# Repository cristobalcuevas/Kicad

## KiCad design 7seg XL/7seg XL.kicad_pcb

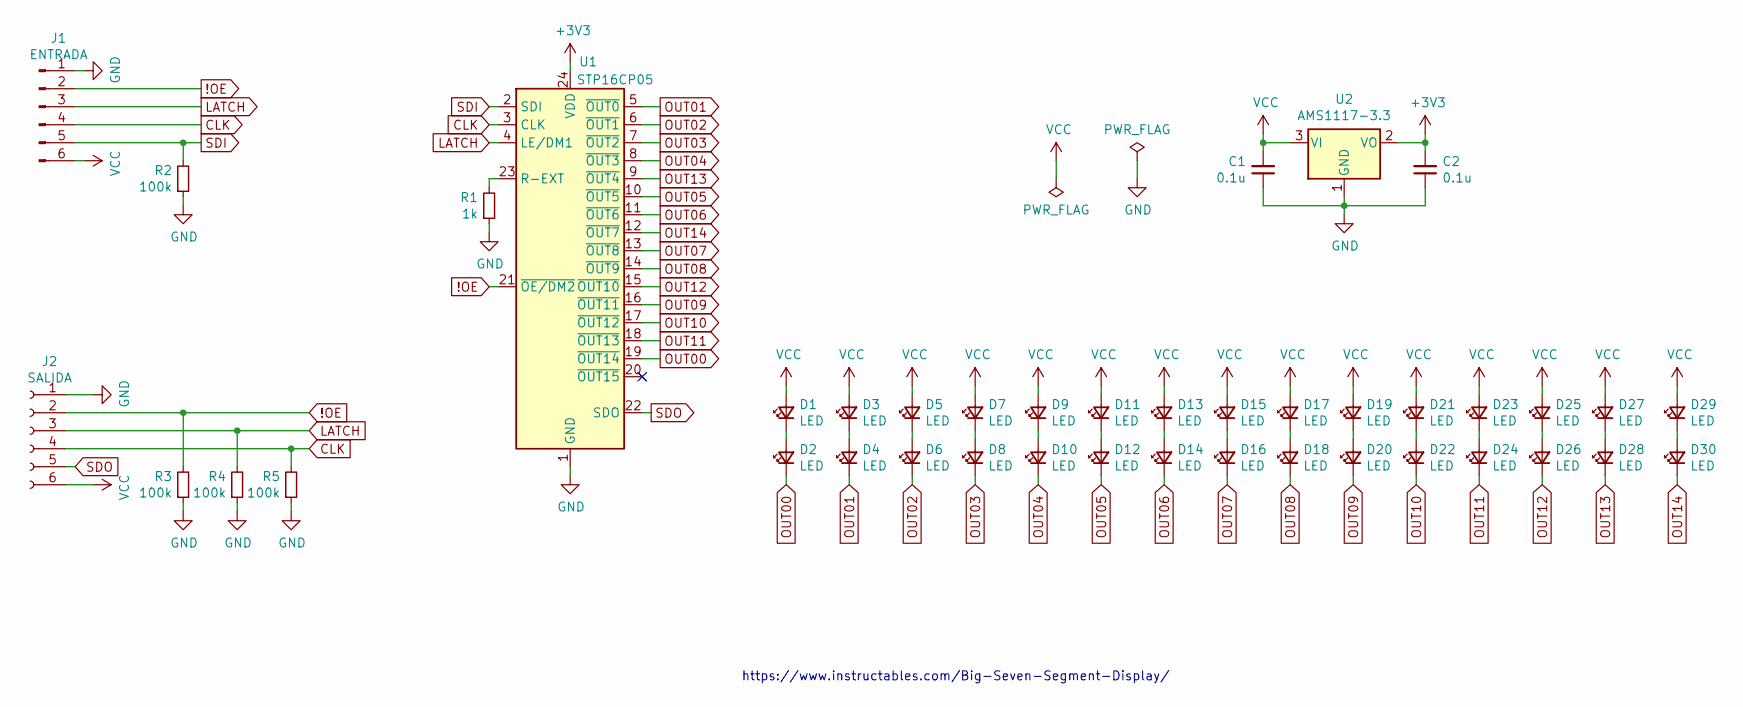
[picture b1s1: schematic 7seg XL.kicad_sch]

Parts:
C1, C2: 0.1u; C_1206_3216Metric
D1, D2, D3, D4, D5, D6, D7, D8, D9, D10, D11, D12, D13, D14, D15, D16, D17, D18, D19, D20, D21, D22, D23, D24, D25, D26, D27, D28, D29, D30: LED; LED_2010_5025Metric_Castellated
J1: ENTRADA; PinHeader_1x06_P2.54mm_Horizontal
J2: SALIDA; PinSocket_1x06_P2.54mm_Horizontal
R1: 1k; R_1206_3216Metric
R2, R3, R4, R5: 100k; R_1206_3216Metric
U1: STP16CP05; TSSOP-24_4.4x7.8mm_P0.65mm
U2: AMS1117-3.3; SOT-223-3_TabPin2

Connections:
!OE: J1.2, J2.2, R3.2, U1.21 (~OE/DM2)
+3V3: C2.2, U1.24 (VDD), U2.2 (VO)
CLK: J1.4, J2.4, R5.2, U1.3 (CLK)
GND: C1.1, C2.1, J1.1, J2.1, R1.1, R2.1, R3.1, R4.1, R5.1, U1.1 (GND), U2.1 (GND)
LATCH: J1.3, J2.3, R4.2, U1.4 (LE/DM1)
unnamed: D1.1 (K), D2.2 (A)
unnamed: D3.1 (K), D4.2 (A)
unnamed: D5.1 (K), D6.2 (A)
unnamed: D7.1 (K), D8.2 (A)
unnamed: D9.1 (K), D10.2 (A)
unnamed: D11.1 (K), D12.2 (A)
unnamed: D13.1 (K), D14.2 (A)
unnamed: D15.1 (K), D16.2 (A)
unnamed: D17.1 (K), D18.2 (A)
unnamed: D19.1 (K), D20.2 (A)
unnamed: D21.1 (K), D22.2 (A)
unnamed: D23.1 (K), D24.2 (A)
unnamed: D25.1 (K), D26.2 (A)
unnamed: D27.1 (K), D28.2 (A)
unnamed: D29.1 (K), D30.2 (A)
unnamed: R1.2, U1.23 (R-EXT)
OUT00: D2.1 (K), U1.19 (~OUT14)
OUT01: D4.1 (K), U1.5 (~OUT0)
OUT02: D6.1 (K), U1.6 (~OUT1)
OUT03: D8.1 (K), U1.7 (~OUT2)
OUT04: D10.1 (K), U1.8 (~OUT3)
OUT05: D12.1 (K), U1.10 (~OUT5)
OUT06: D14.1 (K), U1.11 (~OUT6)
OUT07: D16.1 (K), U1.13 (~OUT8)
OUT08: D18.1 (K), U1.14 (~OUT9)
OUT09: D20.1 (K), U1.16 (~OUT11)
OUT10: D22.1 (K), U1.17 (~OUT12)
OUT11: D24.1 (K), U1.18 (~OUT13)
OUT12: D26.1 (K), U1.15 (~OUT10)
OUT13: D28.1 (K), U1.9 (~OUT4)
OUT14: D30.1 (K), U1.12 (~OUT7)
SDI: J1.5, R2.2, U1.2 (SDI)
SDO: J2.5, U1.22 (SDO)
VCC: C1.2, D1.2 (A), D3.2 (A), D5.2 (A), D7.2 (A), D9.2 (A), D11.2 (A), D13.2 (A), D15.2 (A), D17.2 (A), D19.2 (A), D21.2 (A), D23.2 (A), D25.2 (A), D27.2 (A), D29.2 (A), J1.6, J2.6, U2.3 (VI)

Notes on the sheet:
https://www.instructables.com/Big-Seven-Segment-Display/

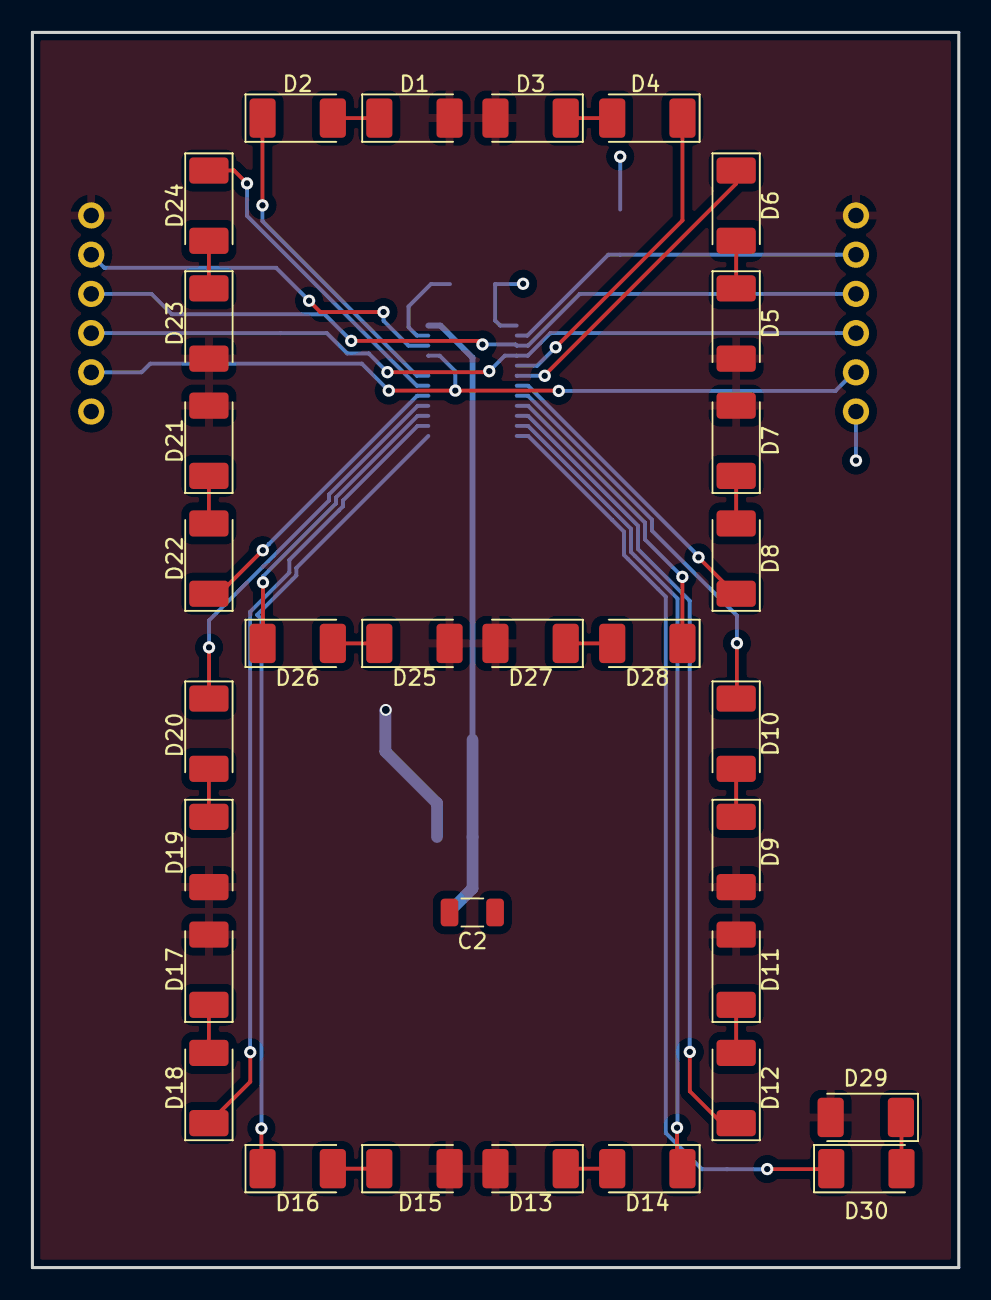
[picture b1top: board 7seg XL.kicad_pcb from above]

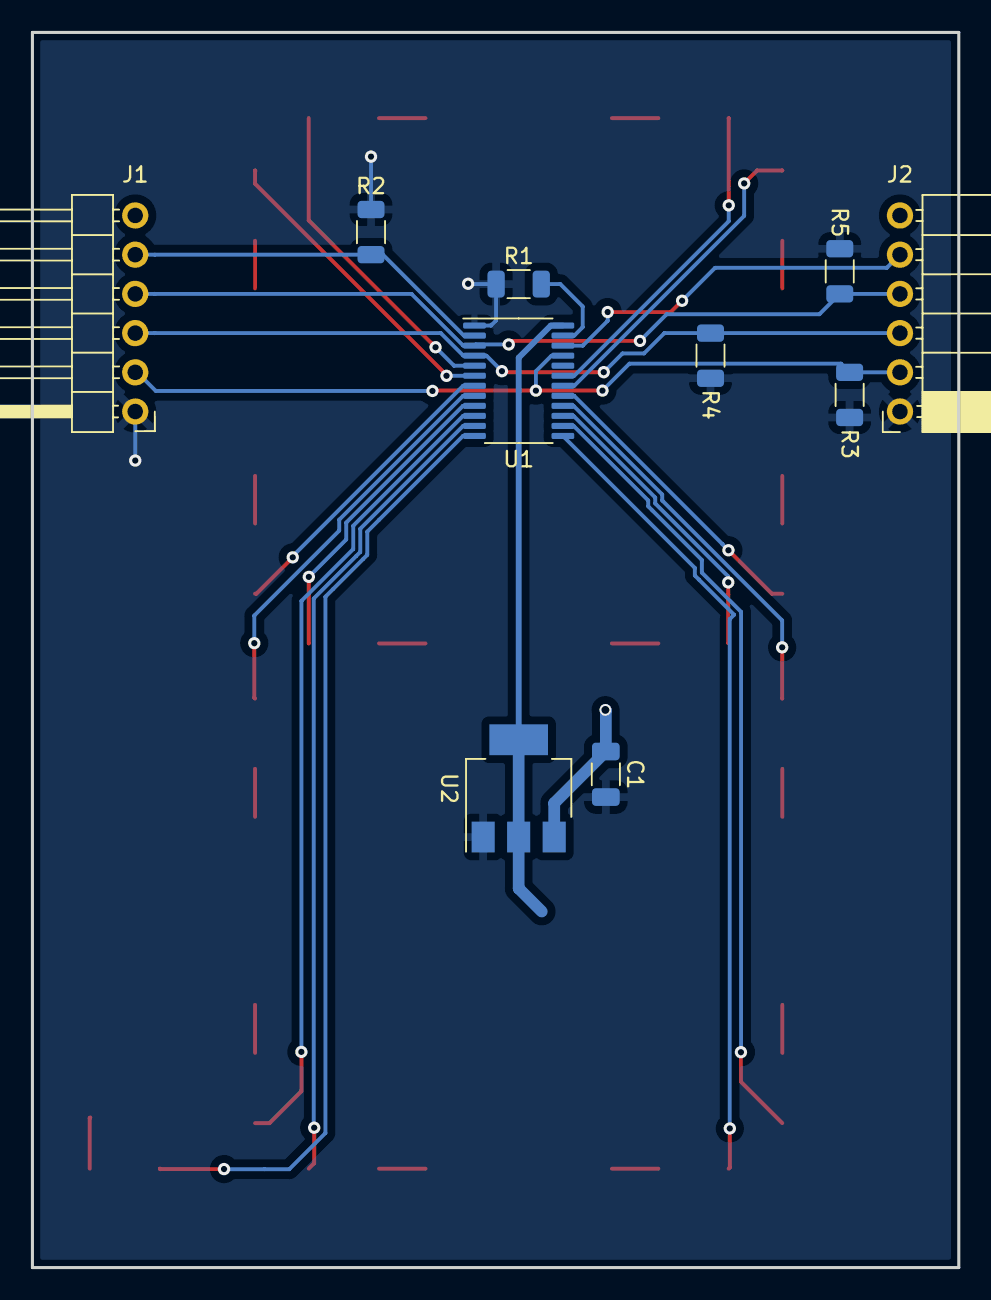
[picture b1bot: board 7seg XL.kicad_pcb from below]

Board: 2 copper layers, 60.0 x 80.0 mm, 41 parts (10 on the bottom side), 39 nets.

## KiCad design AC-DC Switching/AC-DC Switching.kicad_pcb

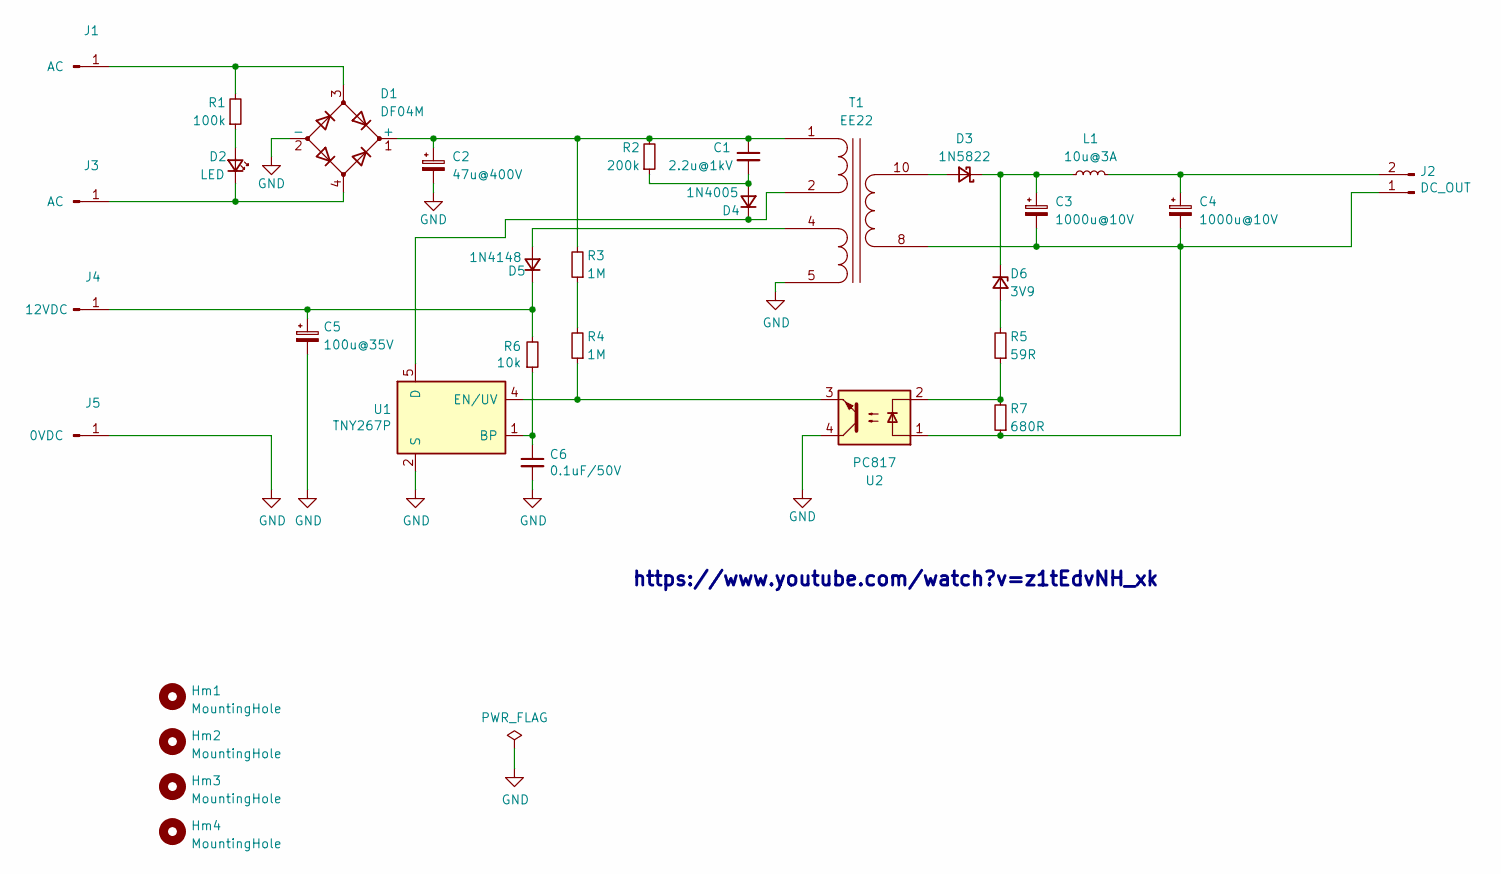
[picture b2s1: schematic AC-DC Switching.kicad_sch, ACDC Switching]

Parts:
C1: 2.2u@1kV; C_Disc_D10.5mm_W5.0mm_P5.00mm
C2: 47u@400V; CP_Radial_D10.0mm_P5.00mm
C3, C4: 1000u@10V; CP_Radial_D12.5mm_P5.00mm
C5: 100u@35V; CP_Radial_D10.0mm_P5.00mm
C6: 0.1uF/50V; C_Rect_L7.2mm_W3.5mm_P5.00mm_FKS2_FKP2_MKS2_MKP2
D1: DF04M; Diode_Bridge_DIP-4_W7.62mm_P5.08mm
D2: LED; LED_D3.0mm
D3: 1N5822; D_DO-201AD_P15.24mm_Horizontal
D4: 1N4005; D_DO-15_P12.70mm_Horizontal
D5: 1N4148; D_DO-34_SOD68_P7.62mm_Horizontal
D6: 3V9; D_DO-41_SOD81_P10.16mm_Horizontal
Hm1, Hm2, Hm3, Hm4: MountingHole; MountingHole_3.2mm_M3
J1, J3: AC
J2: DC_OUT; Molex_KK-254_AE-6410-02A_1x02_P2.54mm_Vertical
J4: 12VDC; TestPoint_Pad_D1.0mm
J5: 0VDC; TestPoint_Pad_D1.0mm
L1: 10u@3A; L_Toroid_Vertical_L21.6mm_W9.1mm_P8.40mm_Bourns_5700
R1: 100k; R_Axial_DIN0207_L6.3mm_D2.5mm_P10.16mm_Horizontal
R2: 200k; R_Axial_DIN0207_L6.3mm_D2.5mm_P10.16mm_Horizontal
R3, R4: 1M; R_Axial_DIN0207_L6.3mm_D2.5mm_P10.16mm_Horizontal
R5: 59R; R_Axial_DIN0207_L6.3mm_D2.5mm_P10.16mm_Horizontal
R6: 10k; R_Axial_DIN0207_L6.3mm_D2.5mm_P10.16mm_Horizontal
R7: 680R; R_Axial_DIN0207_L6.3mm_D2.5mm_P10.16mm_Horizontal
T1: EE22; Transformer_Myrra_EF20_7408x
U1: TNY267P; PowerIntegrations_PDIP-8B
U2: PC817; DIP-4_W7.62mm

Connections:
GND: C2.2, C5.2, C6.2, D1.2 (-), J5.1, T1.5 (SA), U1.2 (S), U1.3 (S), U1.7 (S), U1.8 (S), U2.4
unnamed: C1.1, C2.1, D1.1 (+), R2.2, R3.2, T1.1 (SD)
unnamed: C1.2, D4.2 (A), R2.1
unnamed: C3.1, D3.1 (K), D6.1 (K), L1.1
unnamed: C3.2, C4.2, J2.1, R7.1, T1.8 (AA), U2.1
unnamed: C4.1, J2.2, L1.2
unnamed: C5.1, D5.1 (K), J4.1, R6.2
unnamed: C6.1, R6.1, U1.1 (BP)
unnamed: D1.3, J1.1, R1.2
unnamed: D1.4, D2.1 (K), J3.1
unnamed: D2.2 (A), R1.1
unnamed: D3.2 (A), T1.10 (AB)
unnamed: D4.1 (K), T1.2 (SC), U1.5 (D)
unnamed: D5.2 (A), T1.4 (SB)
unnamed: D6.2 (A), R5.2
unnamed: R3.1, R4.2
unnamed: R4.1, U1.4 (EN/UV), U2.3
unnamed: R5.1, R7.2, U2.2

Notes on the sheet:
https://www.youtube.com/watch?v=z1tEdvNH_xk

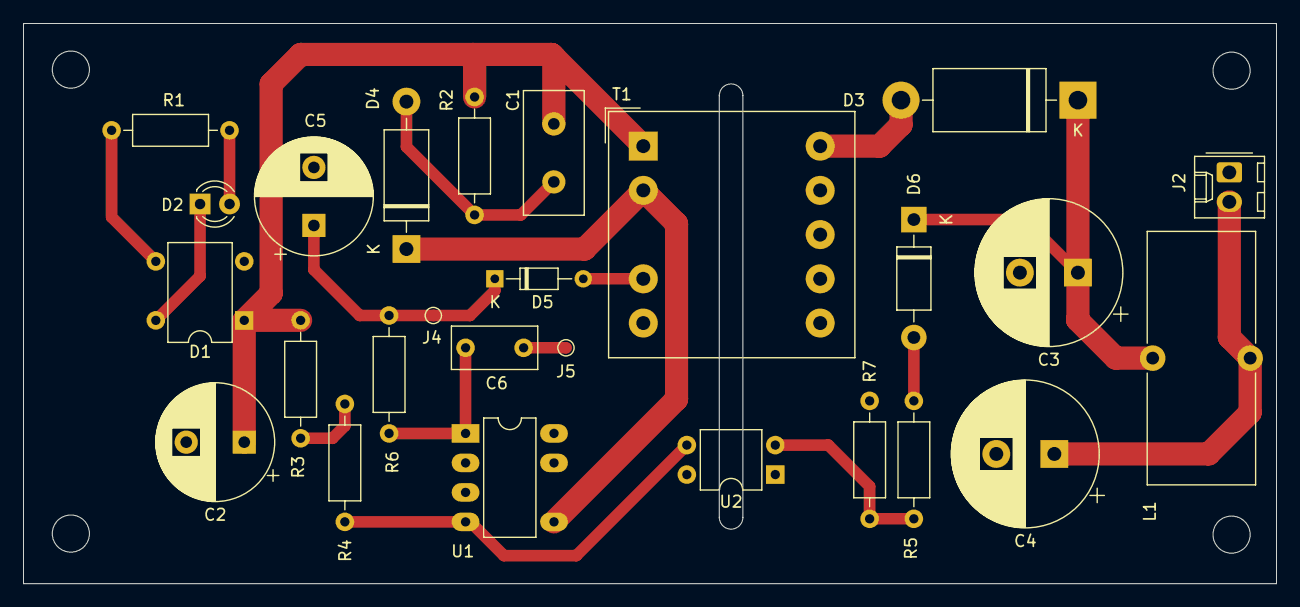
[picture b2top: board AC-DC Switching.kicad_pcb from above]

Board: 2 copper layers, 108.0 x 48.3 mm, 30 parts (0 on the bottom side), 18 nets.

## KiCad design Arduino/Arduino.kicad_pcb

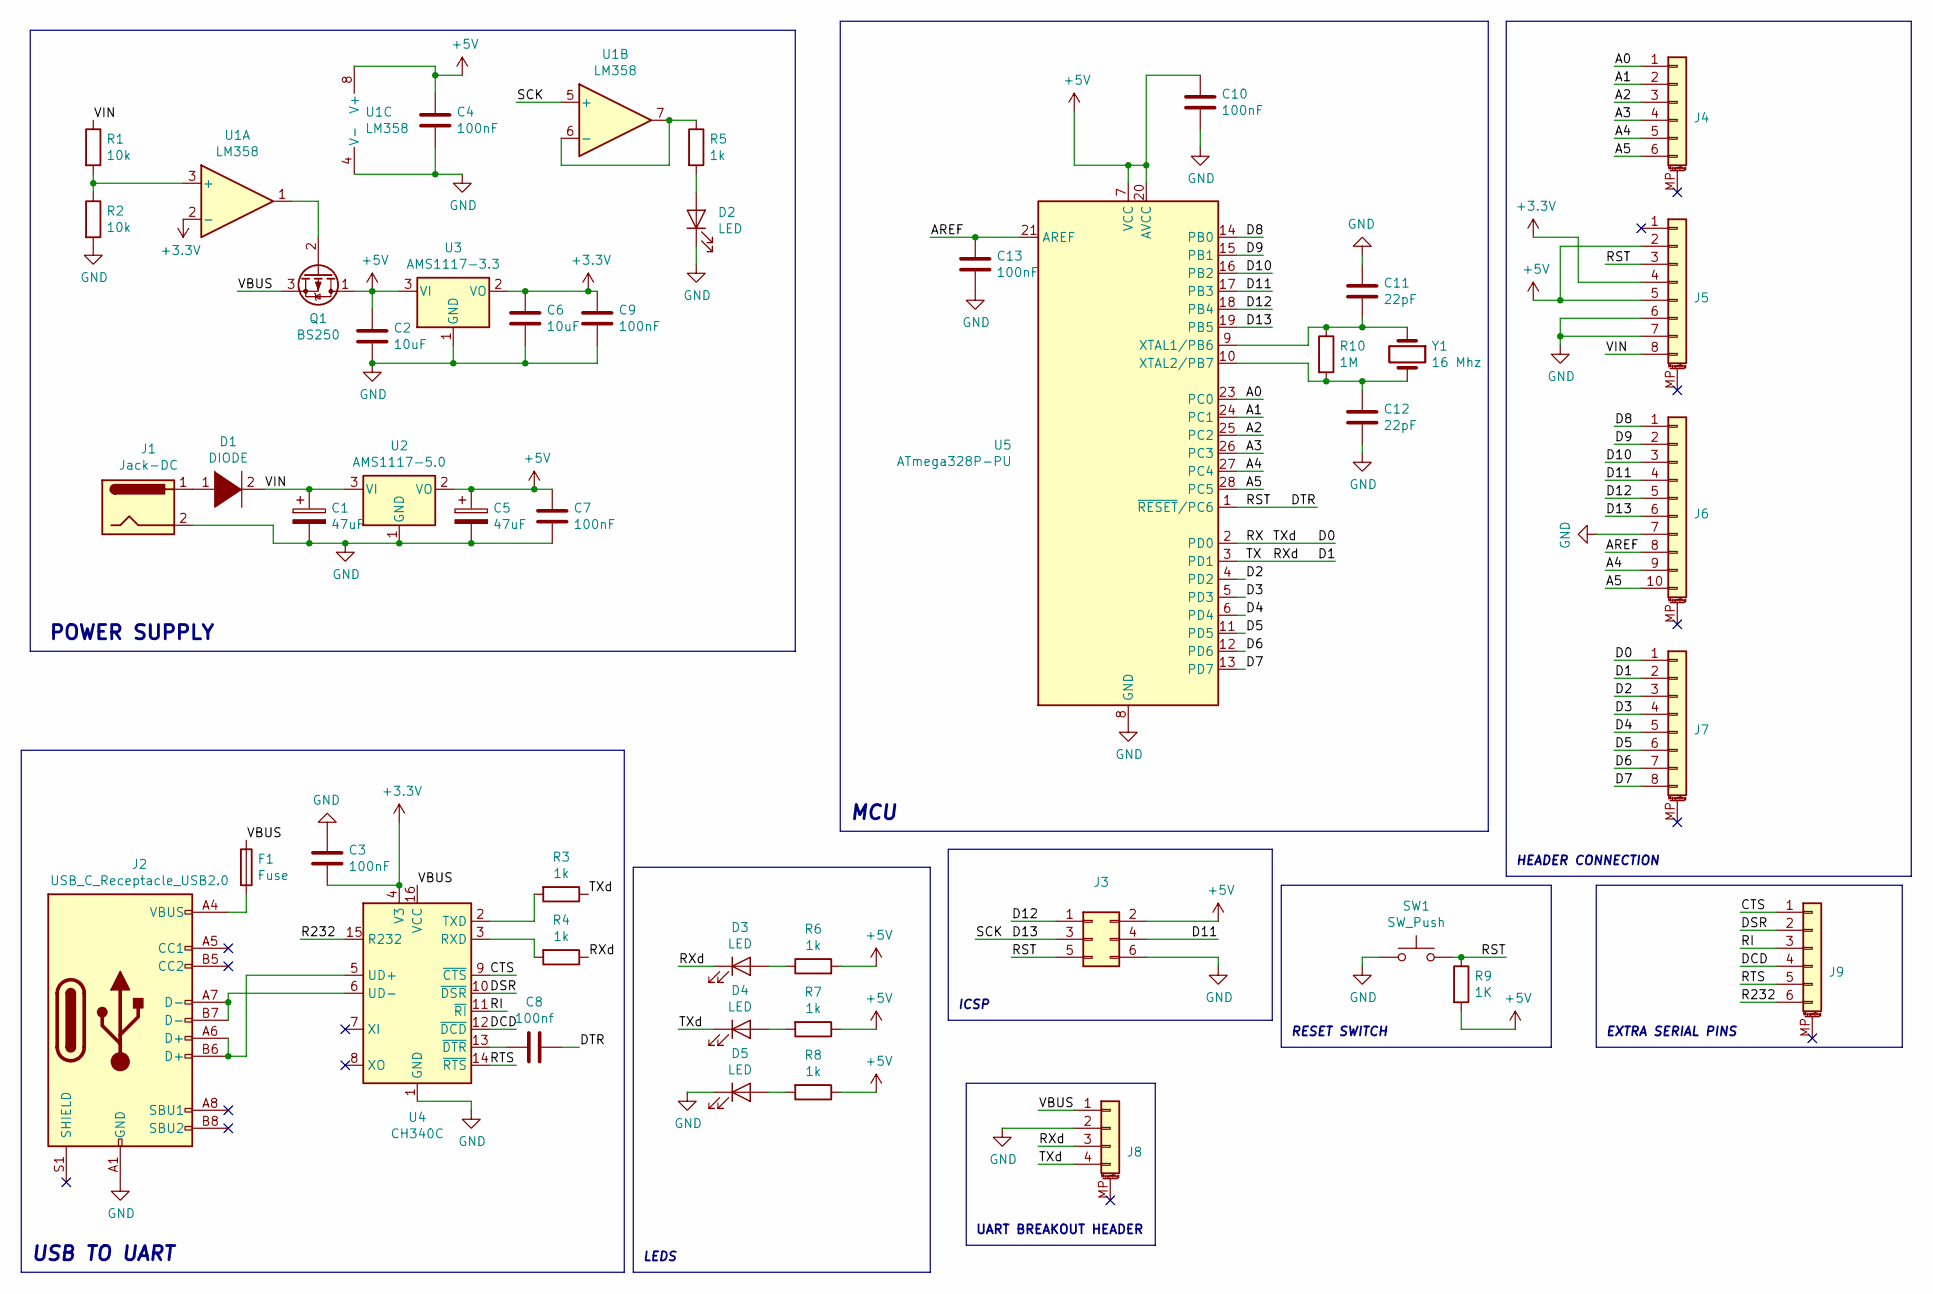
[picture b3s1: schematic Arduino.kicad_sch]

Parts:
C1, C5: 47uF
C2, C6: 10uF
C3, C4, C7, C9, C10, C13: 100nF
C8: 100nf
C11, C12: 22pF
D1: DIODE
D2, D3, D4, D5: LED
F1: Fuse
J1: Jack-DC
J2: USB_C_Receptacle_USB2.0
J3: Conn_02x03_Odd_Even
J4, J9: Conn_01x06_MountingPin
J5, J7: Conn_01x08_MountingPin
J6: Conn_01x10_MountingPin
J8: Conn_01x04_MountingPin
Q1: BS250; TO-92_Inline
R1, R2: 10k
R3, R4, R5, R6, R7, R8: 1k
R9: 1K
R10: 1M
SW1: SW_Push
U1: LM358
U2: AMS1117-5.0; SOT-223-3_TabPin2
U3: AMS1117-3.3; SOT-223-3_TabPin2
U4: CH340C; SOIC-16_3.9x9.9mm_P1.27mm
U5: ATmega328P-PU; DIP-28_W7.62mm
Y1: 16 Mhz

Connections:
+3V3: C3.2, C6.1, C9.1, J5.4, U1.2 (-), U3.2 (VO), U4.4 (V3)
/A0: J4.1, U5.23 (PC0)
/A1: J4.2, U5.24 (PC1)
/A2: J4.3, U5.25 (PC2)
/A3: J4.4, U5.26 (PC3)
/A4: J4.5, J6.9, U5.27 (PC4)
/A5: J4.6, J6.10, U5.28 (PC5)
/AREF: C13.1, J6.8, U5.21 (AREF)
/CTS: J9.1, U4.9 (~CTS)
/D0: D4.1 (K), J7.1, J8.4, R3.1, U5.2 (PD0)
/D1: D3.1 (K), J7.2, J8.3, R4.1, U5.3 (PD1)
/D2: J7.3, U5.4 (PD2)
/D3: J7.4, U5.5 (PD3)
/D4: J7.5, U5.6 (PD4)
/D5: J7.6, U5.11 (PD5)
/D6: J7.7, U5.12 (PD6)
/D7: J7.8, U5.13 (PD7)
/D8: J6.1, U5.14 (PB0)
/D9: J6.2, U5.15 (PB1)
/D10: J6.3, U5.16 (PB2)
/D11: J3.4, J6.4, U5.17 (PB3)
/D12: J3.1, J6.5, U5.18 (PB4)
/D13: J3.3, J6.6, U1.5 (+), U5.19 (PB5)
/DCD: J9.4, U4.12 (~DCD)
/DSR: J9.2, U4.10 (~DSR)
/DTR: C8.1, J3.5, J5.3, R9.1, SW1.2, U5.1 (~RESET/PC6)
/R232: J9.6, U4.15 (R232)
/RI: J9.3, U4.11 (~RI)
/RTS: J9.5, U4.14 (~RTS)
/VBUS: F1.1, J8.1, Q1.3 (S), U4.16 (VCC)
/VIN: C1.1, D1.2 (A), J5.8, R1.1, U2.3 (VI)
GND: C1.2, C2.2, C3.1, C4.2, C5.2, C6.2, C7.2, C9.2, C10.2, C11.1, C12.2, C13.2, D2.1 (K), D5.1 (K), J1.2, J2.A1 (GND), J2.A12 (GND), J2.B1 (GND), J2.B12 (GND), J3.6, J5.6, J5.7, J6.7, J8.2, R2.2, SW1.1, U1.4 (V-), U2.1 (GND), U3.1 (GND), U4.1 (GND), U5.8 (GND), U5.22 (GND); also elsewhere on the board
unnamed: C8.2, U4.13 (~DTR)
unnamed: C11.2, R10.1, U5.9 (XTAL1/PB6), Y1.1
unnamed: C12.1, R10.2, U5.10 (XTAL2/PB7), Y1.2
unnamed: D1.1 (K), J1.1
unnamed: D2.2 (A), R5.2
unnamed: D3.2 (A), R6.1
unnamed: D4.2 (A), R7.2
unnamed: D5.2 (A), R8.2
unnamed: F1.2, J2.A4 (VBUS), J2.A9 (VBUS), J2.B4 (VBUS), J2.B9 (VBUS)
unnamed: J2.A6 (D+), J2.B6 (D+), U4.5 (UD+)
unnamed: J2.A7 (D-), J2.B7 (D-), U4.6 (UD-)
unnamed: R1.2, R2.1, U1.3 (+)
unnamed: R3.2, U4.2 (TXD)
unnamed: R4.2, U4.3 (RXD)
unnamed: R5.1, U1.6 (-), U1.7

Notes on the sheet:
HEADER CONNECTION
LEDS
ICSP
RESET SWITCH
MCU
UART BREAKOUT HEADER
USB TO UART
EXTRA SERIAL PINS
POWER SUPPLY

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
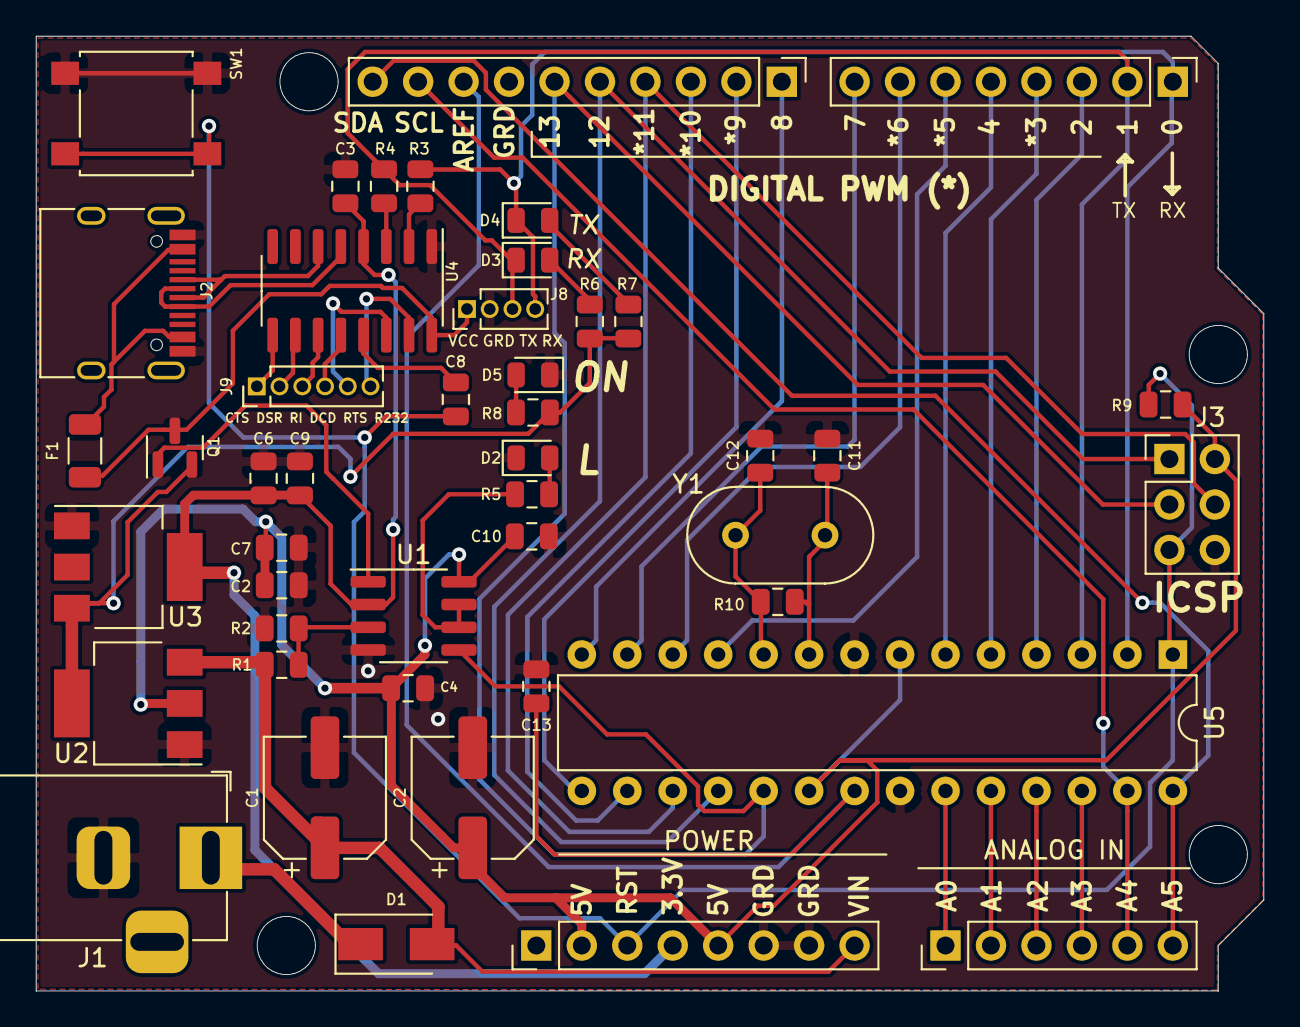
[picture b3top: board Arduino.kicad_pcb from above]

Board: 2 copper layers, 68.6 x 53.3 mm, 46 parts (0 on the bottom side), 49 nets.

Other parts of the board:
C2#2: 10uF; CP_Elec_6.3x5.4

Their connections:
GND: C2#2.2; also elsewhere on the board

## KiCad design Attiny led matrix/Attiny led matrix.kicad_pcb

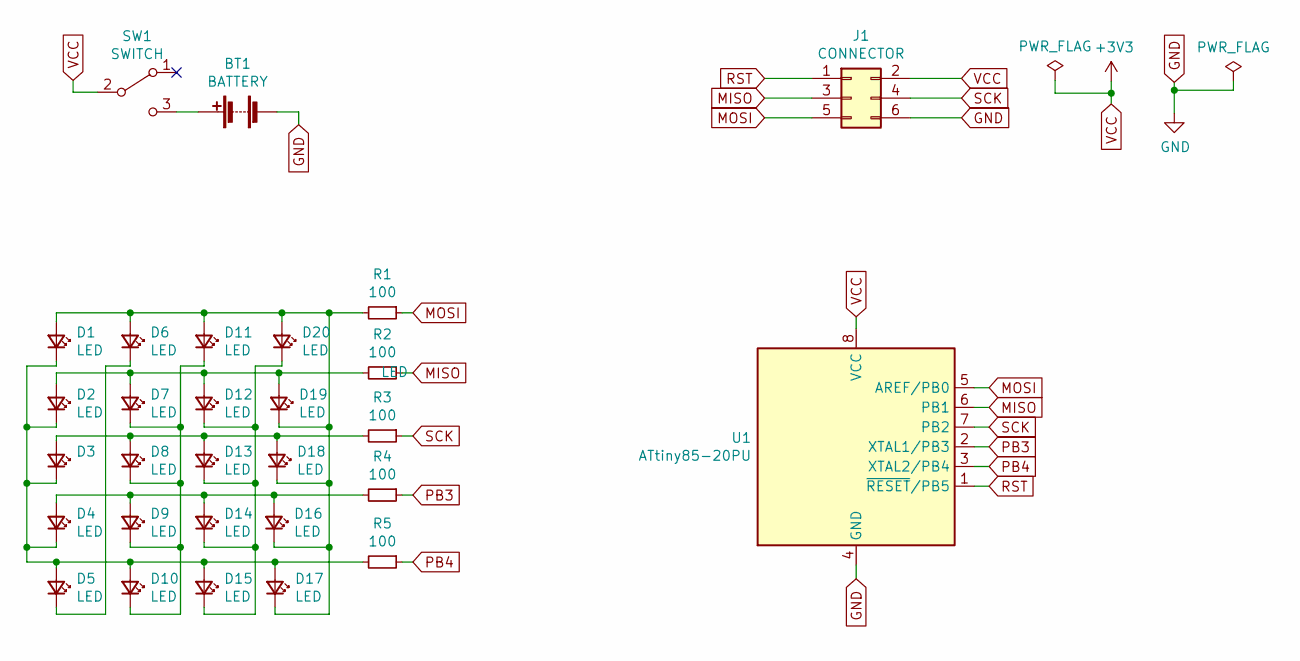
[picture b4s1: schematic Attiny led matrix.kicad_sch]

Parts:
BT1: BATTERY; BatteryHolder_Keystone_103_1x20mm
D1, D2, D3, D4, D5, D6, D7, D8, D9, D10, D11, D12, D13, D14, D15, D16, D17, D18, D19, D20: LED; LED_D3.0mm
J1: CONNECTOR; PinHeader_2x03_P2.54mm_Vertical
R1, R2, R3, R4, R5: 100; R_Axial_DIN0204_L3.6mm_D1.6mm_P5.08mm_Horizontal
SW1: SWITCH; SW_CuK_JS202011CQN_DPDT_Straight
U1: ATtiny85-20PU; DIP-8_W7.62mm

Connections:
GND: BT1.2 (-), J1.6, U1.4 (GND)
MISO: J1.3, R2.1, U1.6 (PB1)
MOSI: J1.5, R1.1, U1.5 (AREF/PB0)
unnamed: BT1.1 (+), SW1.3 (C)
unnamed: D1.1 (K), D2.1 (K), D3.1 (K), D4.1 (K), D5.2 (A), D10.2 (A), D15.2 (A), D17.2 (A), R5.2
unnamed: D1.2 (A), D6.2 (A), D11.2 (A), D16.1 (K), D17.1 (K), D18.1 (K), D19.1 (K), D20.2 (A), R1.2
unnamed: D5.1 (K), D6.1 (K)
unnamed: D7.1 (K), D8.1 (K), D9.1 (K), D10.1 (K), D11.1 (K)
unnamed: D12.1 (K), D13.1 (K), D14.1 (K), D15.1 (K), D20.1 (K)
unnamed: D2.2 (A), D7.2 (A), D12.2 (A), D19.2 (A), R2.2
unnamed: D3.2 (A), D8.2 (A), D13.2 (A), D18.2 (A), R3.2
unnamed: D4.2 (A), D9.2 (A), D14.2 (A), D16.2 (A), R4.2
PB3: R4.1, U1.2 (XTAL1/PB3)
PB4: R5.1, U1.3 (XTAL2/PB4)
RST: J1.1, U1.1 (~RESET/PB5)
SCK: J1.4, R3.1, U1.7 (PB2)
VCC: J1.2, SW1.2 (B), U1.8 (VCC)

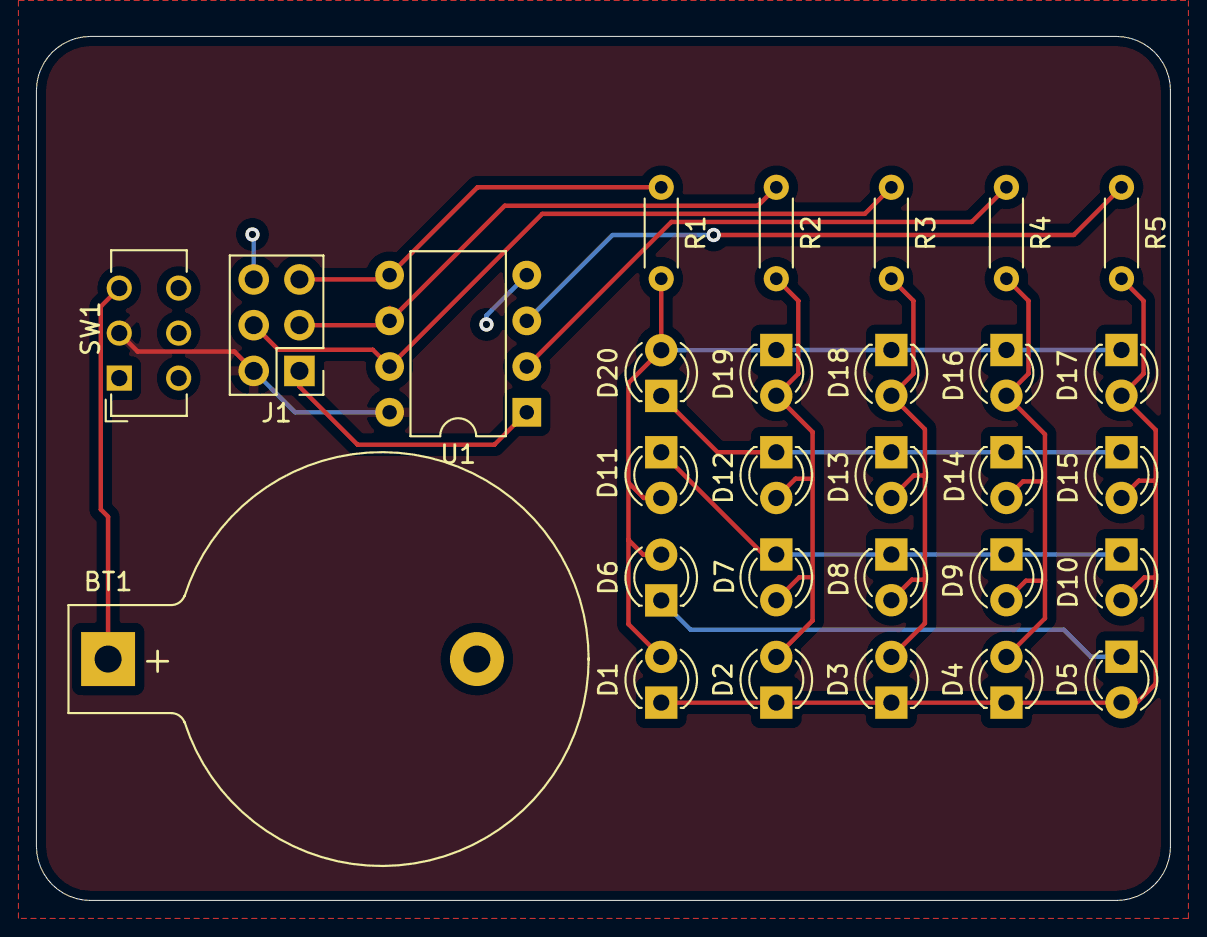
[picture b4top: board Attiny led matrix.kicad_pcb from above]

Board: 2 copper layers, 63.0 x 48.0 mm, 29 parts (0 on the bottom side), 17 nets.

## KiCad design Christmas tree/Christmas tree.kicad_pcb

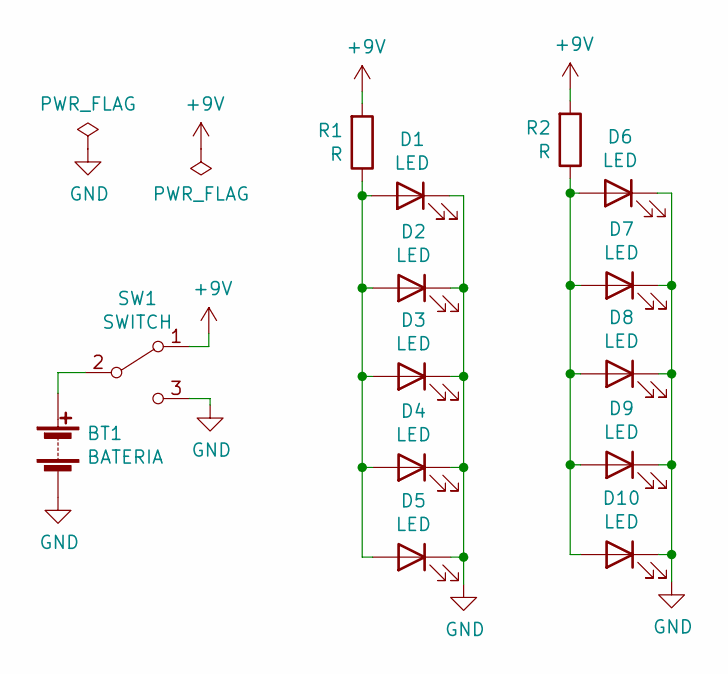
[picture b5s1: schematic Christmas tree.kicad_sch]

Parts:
BT1: BATERIA; PinHeader_1x02_P2.54mm_Vertical
D1, D2, D3, D4, D5, D6, D7, D8, D9, D10: LED; LED_D5.0mm
R1, R2: R; R_Axial_DIN0204_L3.6mm_D1.6mm_P5.08mm_Horizontal
SW1: SWITCH; SW_E-Switch_EG1224_SPDT_Angled

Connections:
+9V: R1.2, R2.2, SW1.1 (A)
GND: BT1.2 (-), D1.1 (K), D2.1 (K), D3.1 (K), D4.1 (K), D5.1 (K), D6.1 (K), D7.1 (K), D8.1 (K), D9.1 (K), D10.1 (K), SW1.3 (C)
unnamed: BT1.1 (+), SW1.2 (B)
unnamed: D1.2 (A), D2.2 (A), D3.2 (A), D4.2 (A), D5.2 (A), R1.1
unnamed: D6.2 (A), D7.2 (A), D8.2 (A), D9.2 (A), D10.2 (A), R2.1

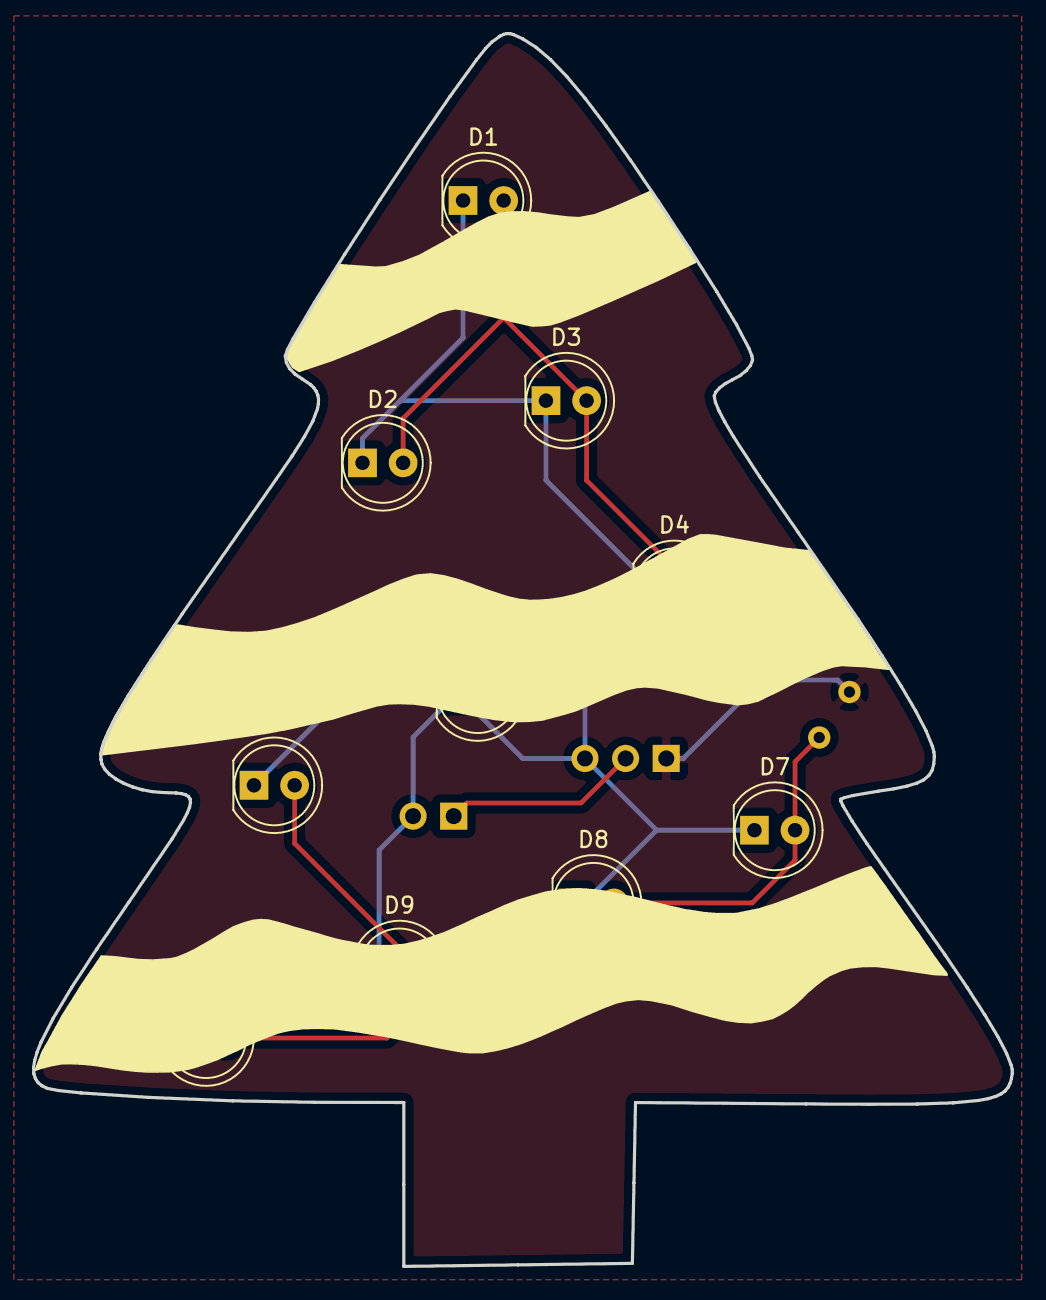
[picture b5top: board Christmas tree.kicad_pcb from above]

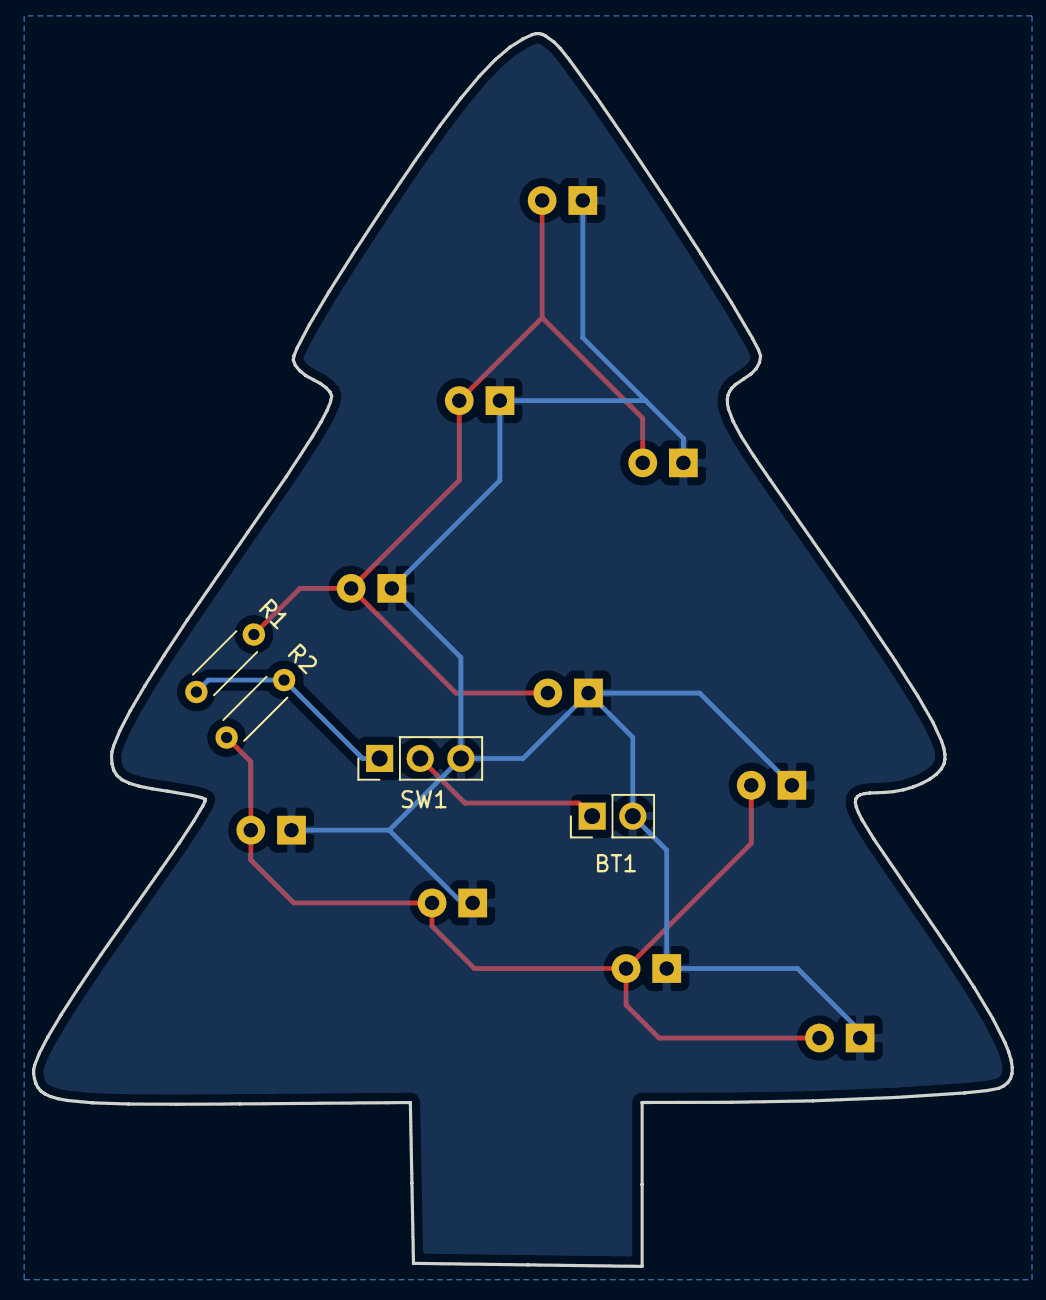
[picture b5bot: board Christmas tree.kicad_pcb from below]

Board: 2 copper layers, 61.2 x 77.1 mm, 14 parts (4 on the bottom side), 5 nets.

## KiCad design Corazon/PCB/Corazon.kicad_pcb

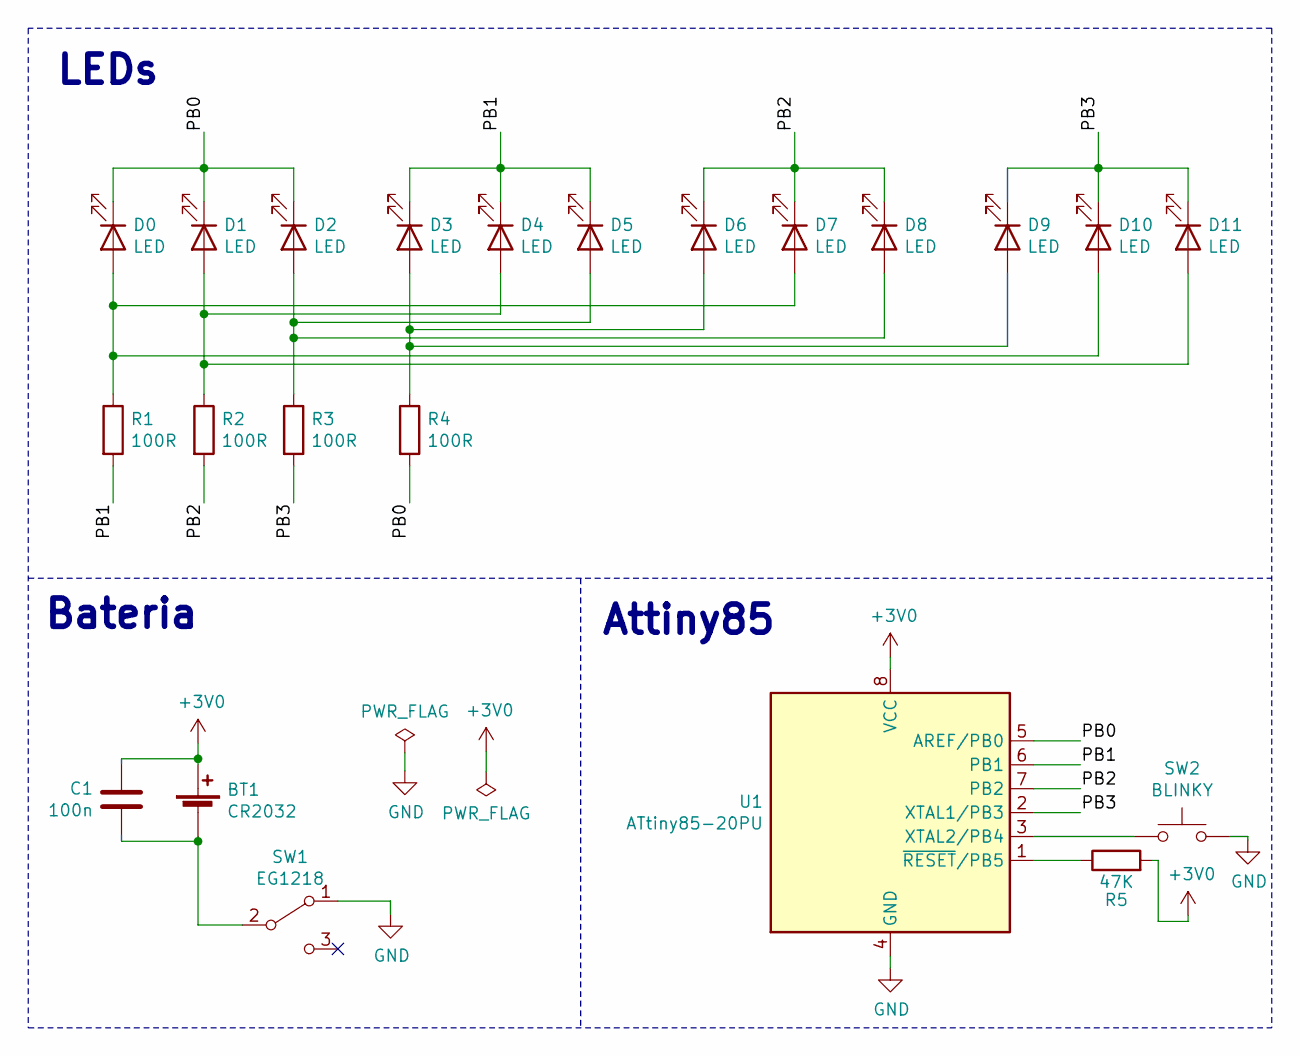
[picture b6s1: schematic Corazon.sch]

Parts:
BT1: CR2032; Batteriehalter_CR2032
C1: 100n; C_0805_2012Metric_Pad1.15x1.40mm_HandSolder
D0, D1, D2, D3, D4, D5, D6, D7, D8, D9, D10, D11: LED; LED_D5.0mm
R1, R2, R3, R4: 100R; R_0805_2012Metric_Pad1.15x1.40mm_HandSolder
R5: 47K; R_0805_2012Metric_Pad1.15x1.40mm_HandSolder
SW1: EG1218; 3Pin_Sensor_SMD
SW2: BLINKY; Taster_SMD_eBay4,5x3mm
U1: ATtiny85-20PU; DIP-8_W7.62mm_Socket

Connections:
+3V0: BT1.1 (+), C1.2, R5.2, U1.8 (VCC)
/PB0: D0.1 (K), D1.1 (K), D2.1 (K), R4.2, U1.5 (AREF/PB0)
/PB1: D3.1 (K), D4.1 (K), D5.1 (K), R1.2, U1.6 (PB1)
/PB2: D6.1 (K), D7.1 (K), D8.1 (K), R2.2, U1.7 (PB2)
/PB3: D9.1 (K), D10.1 (K), D11.1 (K), R3.2, U1.2 (XTAL1/PB3)
GND: SW1.1 (A), SW2.2, U1.4 (GND)
unnamed: BT1.2 (-), C1.1, SW1.2 (B)
unnamed: D0.2 (A), D7.2 (A), D10.2 (A), R1.1
unnamed: D1.2 (A), D4.2 (A), D11.2 (A), R2.1
unnamed: D2.2 (A), D5.2 (A), D8.2 (A), R3.1
unnamed: D3.2 (A), D6.2 (A), D9.2 (A), R4.1
unnamed: R5.1, U1.1 (~RESET~/PB5)
unnamed: SW2.1, U1.3 (XTAL2/PB4)

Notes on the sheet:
LEDs
Bateria
Attiny85
